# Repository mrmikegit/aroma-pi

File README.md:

# Oil Diffuser Control System

A web-based control system for a waterless oil diffuser connected to an HVAC system, designed to run on Raspberry Pi 5.

## Features

- **HVAC Fan Monitoring**: Automatically detects when the HVAC blower fan is running
- **Smart Activation**: Waits 10 seconds after detecting HVAC fan before starting diffuser
- **Configurable Duty Cycles**: 10 different intensity levels (on/off time combinations)
- **Business Hours Control**: Optional scheduling to run only during specified hours
- **Real-time Status**: Live display of HVAC, pump, and fan states
- **Runtime Tracking**: Monitors and displays total runtime for pump and fan
- **Historical Chart**: 24-hour visualization of HVAC fan state
- **Persistent Settings**: All configurations saved and restored after reboot
- **Push Alerts**: Optional web push notifications (including iOS via Add to Home Screen) when the oil tank is empty or via manual test button

## Hardware Requirements

- Raspberry Pi 5
- GPIO Connections:
  - GPIO25: Air pump control (output)
  - GPIO24: 12V fan control (output)
  - GPIO16: HVAC blower fan state (input, no internal pulldown)

## Installation

1. **Update system packages:**
   ```bash
   sudo apt update
   sudo apt upgrade -y
   ```

2. **Install system dependencies:**
   ```bash
   sudo apt install python3-pip python3-venv python3-gpiozero python3-lgpio -y
   ```
   
   Note: `gpiozero` with the `lgpio` backend is required for Raspberry Pi 5 GPIO access.

3. **Create virtual environment and install dependencies:**
   ```bash
   # Create venv with system site packages (required for lgpio access)
   python3 -m venv --system-site-packages venv
   
   # Install Python dependencies
   ./venv/bin/pip install -r requirements.txt
   ```
   
   Or use the install script:
   ```bash
   ./install_deps.sh
   ```

4. **Set up GPIO permissions (if needed):**
   ```bash
   sudo usermod -a -G gpio $USER
   ```
   (Log out and back in for this to take effect)

5. **Configure GPIO16 pull resistor (required for HVAC detection):**
   
   GPIO16 has an internal pull-down resistor enabled by default. This must be disabled for the HVAC fan detection to work correctly.
   
   Edit the boot config file:
   ```bash
   sudo nano /boot/firmware/config.txt
   ```
   
   Add this line at the end of the `[all]` section:
   ```
   gpio=16=ip,pn
   ```
   
   This configures GPIO16 as an input (`ip`) with no pull resistor (`pn`).
   
   Save the file and reboot:
   ```bash
   sudo reboot
   ```
   
   Verify the configuration after reboot:
   ```bash
   pinctrl get 16
   ```
   You should see `pn` (not `pd`) in the output, confirming no pull resistor is enabled.

## Usage

1. **Start the application:**
   
   Easiest way (using the start script):
   ```bash
   ./start.sh
   ```
   
   Or using the virtual environment directly:
   ```bash
   ./venv/bin/python app.py
   ```
   
   Or activate the virtual environment first:
   ```bash
   source venv/bin/activate
   python app.py
   ```

2. **Access the web interface:**
   Open a web browser and navigate to:
   ```
   http://raspberry-pi-ip-address:8080
   ```
   Or if running locally:
   ```
   http://localhost:8080
   ```

3. **Configure the system:**
   - Enable/disable the aroma system
   - Select desired intensity (duty cycle)
   - Optionally enable business hours
   - Monitor real-time status and runtime

## Duty Cycles

The system supports 10 different intensity levels:

| On Time | Off Time | Intensity |
|---------|----------|-----------|
| 60s     | 240s     | Very Low  |
| 60s     | 120s     | Low       |
| 60s     | 90s      | Medium-Low|
| 60s     | 60s      | Medium    |
| 60s     | 45s      | Medium-High|
| 60s     | 30s      | High      |
| 90s     | 30s      | Very High |
| 120s    | 30s      | Very High |
| 240s    | 30s      | Maximum   |
| 360s    | 30s      | Maximum   |

## Operation Logic

1. The system polls GPIO16 every 5 seconds to check HVAC fan state
2. When HVAC fan is detected (logic LOW), the system waits 10 seconds
3. After the delay, the diffuser starts operating with the selected duty cycle
4. The diffuser only runs when:
   - System is enabled
   - HVAC fan is running
   - Within business hours (if enabled)

## Auto-Start on Boot

To run the application automatically on boot, set up a systemd service:

1. **Copy the service file to systemd directory:**
   ```bash
   sudo cp aroma-pi.service /etc/systemd/system/
   ```

2. **Edit the service file to match your setup (if needed):**
   ```bash
   sudo nano /etc/systemd/system/aroma-pi.service
   ```
   
   Update the following if your paths are different:
   - `User=pi` - Change to your username if different
   - `WorkingDirectory=/home/pi/aroma-pi` - Change to your actual path
   - `ExecStart=/home/pi/aroma-pi/venv/bin/python` - Change to your venv path

3. **Reload systemd and enable the service:**
   ```bash
   sudo systemctl daemon-reload
   sudo systemctl enable aroma-pi.service
   ```

4. **Start the service:**
   ```bash
   sudo systemctl start aroma-pi.service
   ```

5. **Check service status:**
   ```bash
   sudo systemctl status aroma-pi.service
   ```

6. **View service logs (to debug GPIO issues):**
   ```bash
   sudo journalctl -u aroma-pi.service -f
   ```

**Useful commands:**
- Stop the service: `sudo systemctl stop aroma-pi.service`
- Restart the service: `sudo systemctl restart aroma-pi.service`
- Disable auto-start: `sudo systemctl disable aroma-pi.service`
- Check if service is enabled: `sudo systemctl is-enabled aroma-pi.service`

## Push Notifications

The app can send web push notifications (including iOS 16.4+ web push when the site is added to the home screen). Notifications are triggered automatically when the oil tank reaches 0% and can be tested via the “Send Test Notification” button in the Control Panel.

1. **HTTPS is required** (you already have this via Cloudflare Zero Trust tunnel). Browsers (especially iOS) only allow service workers and push notifications on secure origins.
2. **Install to Home Screen on iOS**: After opening the site in Safari, tap share → “Add to Home Screen”. Push notifications only work for installed web apps on iOS.
3. **Enable notifications in the UI**: Use the “Enable Notifications” button to grant permission and subscribe the current browser.
4. **VAPID keys**: On first run the server automatically generates a `vapid.json` file. You can replace it with your own keys if desired.
5. **Subscriptions**: Stored in `subscriptions.json`. If a device unregisters, stale subscriptions are removed automatically the next time a notification is sent.

Push endpoints exposed by the server:

- `GET /api/vapid-public-key` – returns the public VAPID key.
- `POST /api/subscribe` – stores a new push subscription (called by the browser).
- `POST /api/test_notification` – sends a test notification to all active subscribers.

If you change domains or certificates, users must re-enable notifications so the browser can create a new subscription.

## File Structure

```
aroma/
├── app.py              # Main Flask application
├── requirements.txt    # Python dependencies
├── start.sh            # Start script
├── install_deps.sh     # Dependency installation script
├── aroma-pi.service    # systemd service file
├── config.json         # Saved settings (auto-generated)
├── history.json        # HVAC history data (auto-generated)
├── vapid.json          # VAPID keys for push notifications (auto-generated)
├── subscriptions.json  # Push notification subscriptions (auto-generated)
├── test_hvac.py        # HVAC testing utility
├── test_push.py        # Push notification testing utility
├── templates/
│   └── index.html      # Web interface
└── static/
    ├── css/
    │   └── style.css   # Stylesheet
    ├── js/
    │   └── app.js      # Frontend JavaScript
    ├── sw.js           # Service worker for push notifications
    ├── manifest.json   # Web app manifest
    └── favicon.svg     # App icon
```

## API Endpoints

- `GET /` - Main web interface
- `GET /api/status` - Get current system status
- `GET /api/history` - Get HVAC history (last 24 hours)
- `GET /api/duty_cycles` - Get available duty cycles
- `POST /api/settings` - Update system settings
- `POST /api/reset_counters` - Reset runtime counters

## Troubleshooting

- **GPIO not working**: Ensure you have GPIO permissions and RPi.GPIO is installed
- **Web interface not accessible**: Check firewall settings and ensure port 8080 is open
- **Settings not persisting**: Check file permissions on `config.json` and `history.json`

## Development Mode

For development on a non-Raspberry Pi system, the application will use mock GPIO that prints to console instead of controlling actual pins.

## License

This project is provided as-is for personal use.

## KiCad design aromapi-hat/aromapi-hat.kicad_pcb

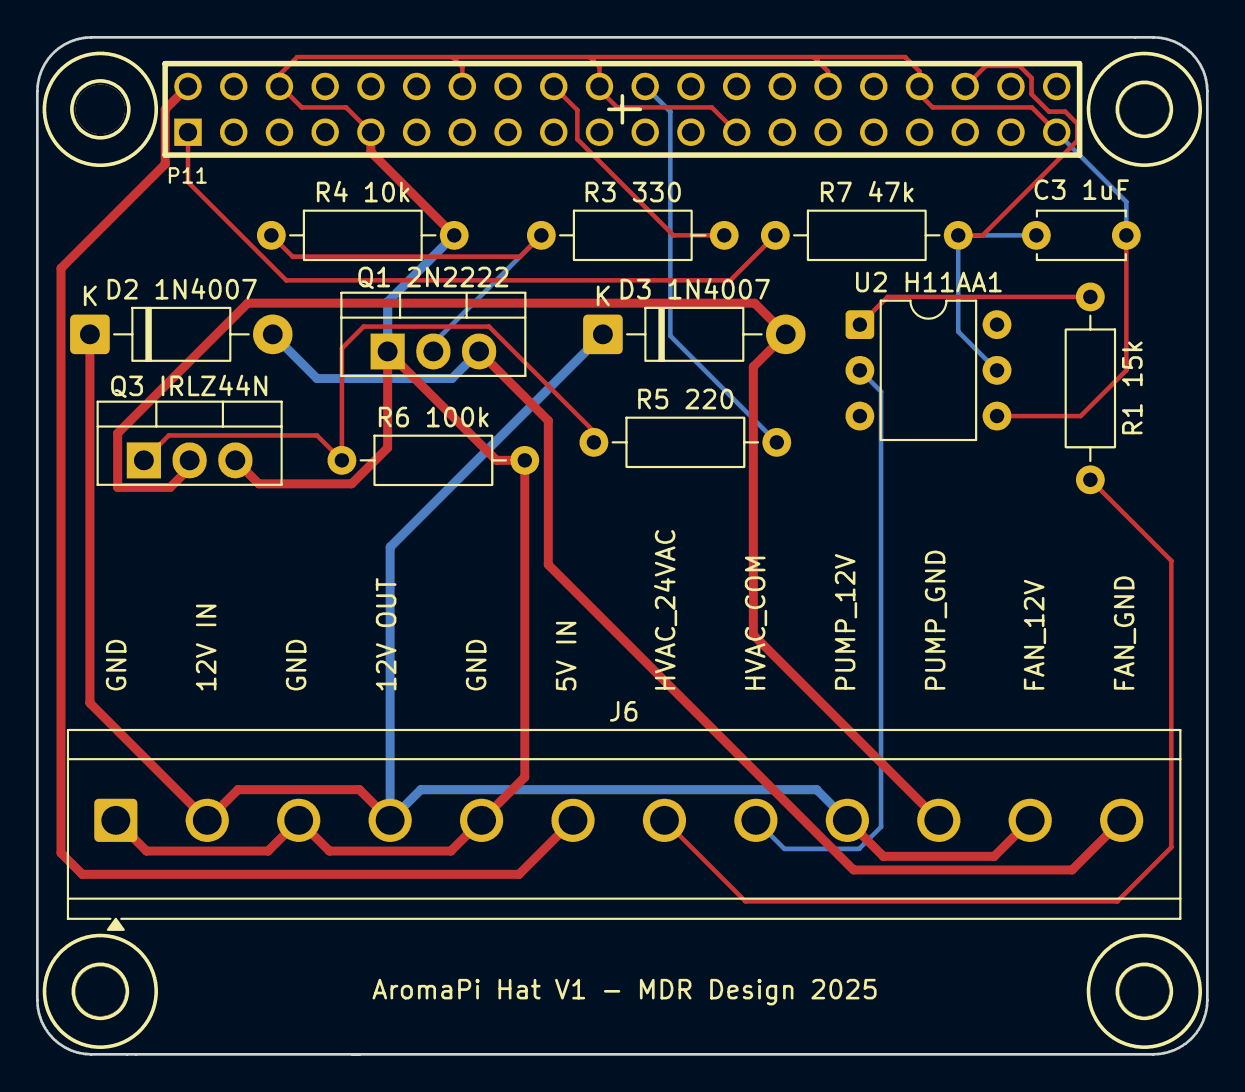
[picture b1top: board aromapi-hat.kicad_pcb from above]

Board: 2 copper layers, 65.0 x 56.5 mm, 18 parts (0 on the bottom side), 14 nets.

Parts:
C3 1uF: 1uF; C_Disc_D4.7mm_W2.5mm_P5.00mm
D2 1N4007, D3 1N4007: 1N4007; D_DO-41_SOD81_P10.16mm_Horizontal
H1, H2, H3, H4: DRILL; dsk-drill-rpi-hat
J6: Screw_Terminal_01x12; TerminalBlock_CUI_TB007-508-12_1x12_P5.08mm_Horizontal
P11: CONN_20X2; PIN_ARRAY_20X2
Q1 2N2222: 2N2222; TO-220-3_Vertical
Q3 IRLZ44N: IRLZ44N; TO-220-3_Vertical
R1 15k: 15K; R_Axial_DIN0207_L6.3mm_D2.5mm_P10.16mm_Horizontal
R3 330: 330; R_Axial_DIN0207_L6.3mm_D2.5mm_P10.16mm_Horizontal
R4 10k: 10k; R_Axial_DIN0207_L6.3mm_D2.5mm_P10.16mm_Horizontal
R5 220: 100; R_Axial_DIN0207_L6.3mm_D2.5mm_P10.16mm_Horizontal
R6 100k: 100k; R_Axial_DIN0207_L6.3mm_D2.5mm_P10.16mm_Horizontal
R7 47k: 47k; R_Axial_DIN0207_L6.3mm_D2.5mm_P10.16mm_Horizontal
U2 H11AA1: H11AA1; DIP-6_W7.62mm

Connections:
+3.3V: P11.1, R7 47k.1
+5V: J6.6, P11.2
+12V: D2 1N4007.1 (K), D3 1N4007.1 (K), J6.2, J6.4, J6.9, J6.11
Fan: D2 1N4007.2 (A), J6.12, Q1 2N2222.3 (C)
GND: C3 1uF.2, J6.1, J6.3, J6.5, P11.6, P11.9, P11.14, P11.20, P11.25, P11.30, P11.34, P11.39, Q1 2N2222.1 (E), Q3 IRLZ44N.3 (S), R4 10k.2, R6 100k.2, U2 H11AA1.4
GPIO16_HVAC: C3 1uF.1, P11.36, R7 47k.2, U2 H11AA1.5
GPIO24_FAN: P11.18, R3 330.2
GPIO25_PUMP: P11.22, R5 220.2
HVAC+: J6.7, R1 15k.2
HVAC-: J6.8, U2 H11AA1.2
unnamed: Q1 2N2222.2 (B), R3 330.1, R4 10k.1
unnamed: Q3 IRLZ44N.1 (G), R5 220.1, R6 100k.1
unnamed: R1 15k.1, U2 H11AA1.1
Pump: D3 1N4007.2 (A), J6.10, Q3 IRLZ44N.2 (D)

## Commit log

2025-11-16 init
2025-11-16 add favicon and change defaults
2025-11-16 Add auto off when fuel gauge is empty
2025-11-16 change dir to aroma-pi
2025-11-16 rename to aroma-pi.service
2025-11-18 push notifications
2025-11-18 Push Notification Test
2025-11-18 Push test
2025-12-06 refactor: Streamline dependency installation by leveraging system `lgpio` and update README to reflect simplified setup and new project files.
2025-12-06 feat: Configure HVAC GPIO to disable internal pull resistors using `lgpio.SET_BIAS_DISABLE` and remove `InputDevice` instantiation in tests.
2025-12-06 fix: Correctly configure GPIO16 pull resistor using `lgpio.gpio_set_pull` and add persistent configuration instructions to the README.
2025-12-11 feat: add initial KiCad project for aromapi-hat and update app.py
2025-12-11 feat: add new duty cycle options and labels to the intensity selector.
